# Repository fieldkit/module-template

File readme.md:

# Module Template
This is a template project for creating new FieldKit module hardware in Kicad.

It Has : 
* The board outline.
* A connector to attach it to a FieldKit station.
* 3.3v Regulation.
* An EEPROM to identify the module and store any calibration data.

Just clone and augment!

## License Information

> *"In the long history of humankind (and animal kind, too) those who learned to collaborate and improvise most effectively have prevailed."*
>  --**Charles Darwin**

This hardware is released under **CERN Open Hardware License Version 2 - Permissive (CERN-OHL_P)**
Obviously, it's Distributed as-is; and no warranty is given.

---
*Module Template was Designed by Bradley Gawthrop for FieldKit.*

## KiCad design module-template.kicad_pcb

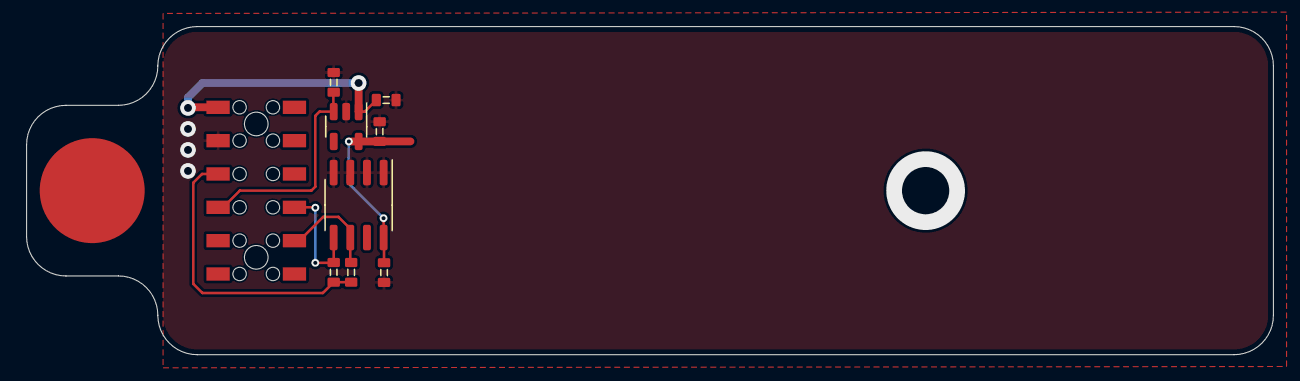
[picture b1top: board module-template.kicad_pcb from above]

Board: 2 copper layers, 95.0 x 25.0 mm, 9 parts (0 on the bottom side), 7 nets.

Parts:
C1, C2: 1µf; R0603
C3: .1μf; R0603
J1: Conn_01x12; M20-7810645R
R1: 10kΩ; R0603
R2, R3: 4.7kΩ; R0603
U1: AP2127K-3.3; SOT-23-5
U2: M24C64-DFMN6TP; SOIC-8_3.9x4.9mm_P1.27mm

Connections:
/Module-Prerequisites/3V3: C2.1, C3.1, U1.5 (VOUT), U2.8 (VCC)
/Module-Prerequisites/ENABLE: J1.4, R1.1, U1.3 (EN)
/Module-Prerequisites/HOST-3V3: J1.3, R2.2, R3.2
/Module-Prerequisites/SCL: J1.8, R2.1, U2.6 (SCL)
/Module-Prerequisites/SDA: J1.9, R3.1, U2.5 (SDA)
/Module-Prerequisites/VIN: C1.1, J1.1, U1.1 (VIN)
GND: C1.2, C2.2, C3.2, J1.2, R1.2, U1.2 (GND), U2.1 (E0), U2.2 (E1), U2.3 (E2), U2.4 (VSS)

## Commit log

2023-08-16 Blank Initialization
2023-08-16 Added PCB Essentials
2023-08-16 PCB Notes, Sheet size adjustment.
2023-08-17 Schematic structure
2023-08-17 Work on Prerequisites sheet
2023-08-17 Finished prerequisites. Started component placement.
2023-08-17 Board routing complete.
2023-08-17 Fixing PDF issues.
2023-08-17 Cleaning up file system.
2023-08-17 Troubleshooting.
2023-08-17 More Troubleshooting. grr.
2024-03-01 Small aesthetic channges, and KiCad version update.
